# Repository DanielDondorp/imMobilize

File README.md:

# imMobilize
### Open software and hardware to do behavioural analysis of small swimming animals.

## How is this

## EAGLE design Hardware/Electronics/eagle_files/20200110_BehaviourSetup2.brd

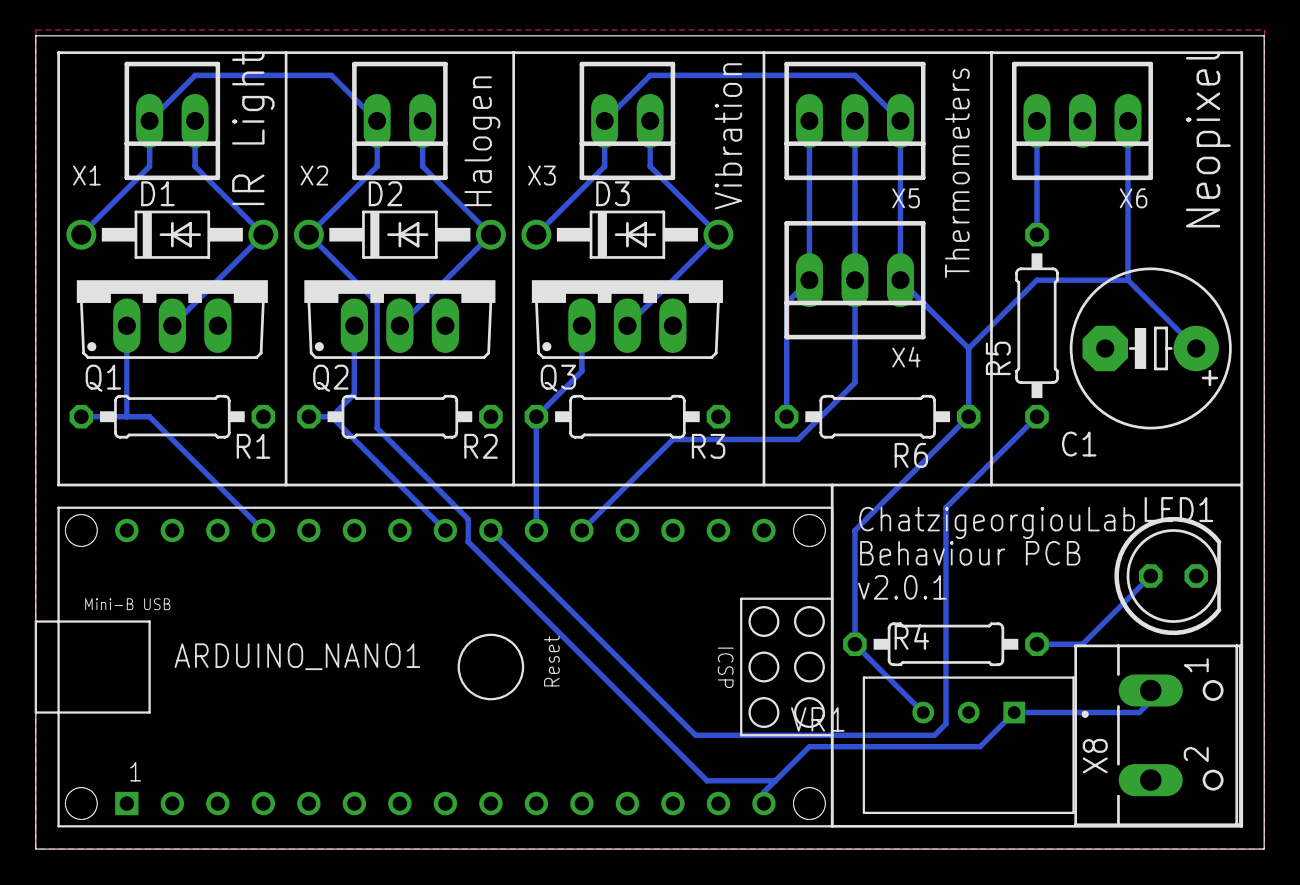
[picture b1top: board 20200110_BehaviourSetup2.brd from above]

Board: 2 copper layers, 68.6 x 45.4 mm, 23 parts (0 on the bottom side), 14 nets.

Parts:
ARDUINO_NANO1: ARDUINO_NANO
C1: 1000uF; E5-8,5
D1, D2, D3: 1N4004; DO41-10
LED1: LED5MM
Q1, Q2, Q3: IRF540; TO220BV
R1, R2, R3: 10k; 0207/10
R4: 220; 0207/10
R5: 330; 0207/10
R6: 4.7k; 0207/10
VR1: TSR_1-2450; CONV_TSR_1-2450
X1, X2, X3: 22-23-2021
X4, X5, X6: 22-23-2031
X8: W237-102

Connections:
+5V: C1.+, D3.C, R4.1, R6.1, VR1.3, X3.2, X4.1, X5.1, X6.1
+12V: ARDUINO_NANO1.15, D1.C, D2.C, VR1.1, X1.2, X2.2, X8.1
GND: ARDUINO_NANO1.14, ARDUINO_NANO1.19, C1.-, LED1.K, Q1.S, Q2.S, Q3.S, R1.2, R2.2, R3.2, VR1.2, X6.2, X8.2
unnamed: ARDUINO_NANO1.27, Q1.G, R1.1
unnamed: ARDUINO_NANO1.23, Q2.G, R2.1
unnamed: ARDUINO_NANO1.21, Q3.G, R3.1
unnamed: D3.A, Q3.D, X3.1
unnamed: LED1.A, R4.2
unnamed: R6.2, X4.3, X5.3
unnamed: ARDUINO_NANO1.20, X4.2, X5.2
unnamed: ARDUINO_NANO1.22, R5.1
unnamed: R5.2, X6.3
unnamed: D2.A, Q2.D, X2.1
unnamed: D1.A, Q1.D, X1.1

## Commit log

2018-03-20 Update Arduino.py, Camera.py, and 5 more files...
2018-04-13 Update __main__.py, arduino.py, and 4 more files...
2018-04-17 Update stimulimanager.py
    Fixed error "Name elapsed not defined"
2018-04-17 Update __main__.py
    Fixed typo "exposture" to "exposure" in metadata dataframe
2018-04-17 Update stimulimanager.py
    Trying to fix stim timings
2018-05-07 Minor bugfixes
    1. Age not recorded. Call to spinBoxAge missed .value(). Called full object instead.
    2. Drug and Genetic names revert back to none when unchecked at time of starting experiment.
2018-06-29 Update IM.bmp, IM.png, and 8 more files...
2018-08-14 Update __main__.py, __mainlazy__.py, and 6 more files...
2019-02-08 Update __main__.py, form.py, and form.ui Updated the way hatching times are submitted by the user.
2019-02-08 Update __main__.py Fixed an error in how the hatching time userinput is checked for errors.
2019-12-02 Shuffled a bunch of files around
2020-01-06 Restructured folder
2020-01-06 Restructured
2020-01-10 Added information for the electronics
2020-01-13 expanded readme
2020-01-13 added requirements
2020-01-13 added ReadMe_data
2020-01-13 preparing to remove old readme
2020-01-13 removed old readme
2020-01-13 gathered all hardware files in one folder
2020-01-13 remove old hardware folders
2020-01-13 Create LICENSE
2020-01-13 hardware guide started
2020-01-15 changed eagle files to include 1N4004 diode in design
2020-01-15 adding more guides
2020-01-15 added images for guides
2020-01-15 updated schematics to include correct power converter
2020-01-17 Changed circuitry, rebuilt PCB
2020-01-20 updated __main__ to automatically set home dir if D:\ is not found
2020-01-20 altered window name from Stimuli and Trigger Delivery to imMobilize
